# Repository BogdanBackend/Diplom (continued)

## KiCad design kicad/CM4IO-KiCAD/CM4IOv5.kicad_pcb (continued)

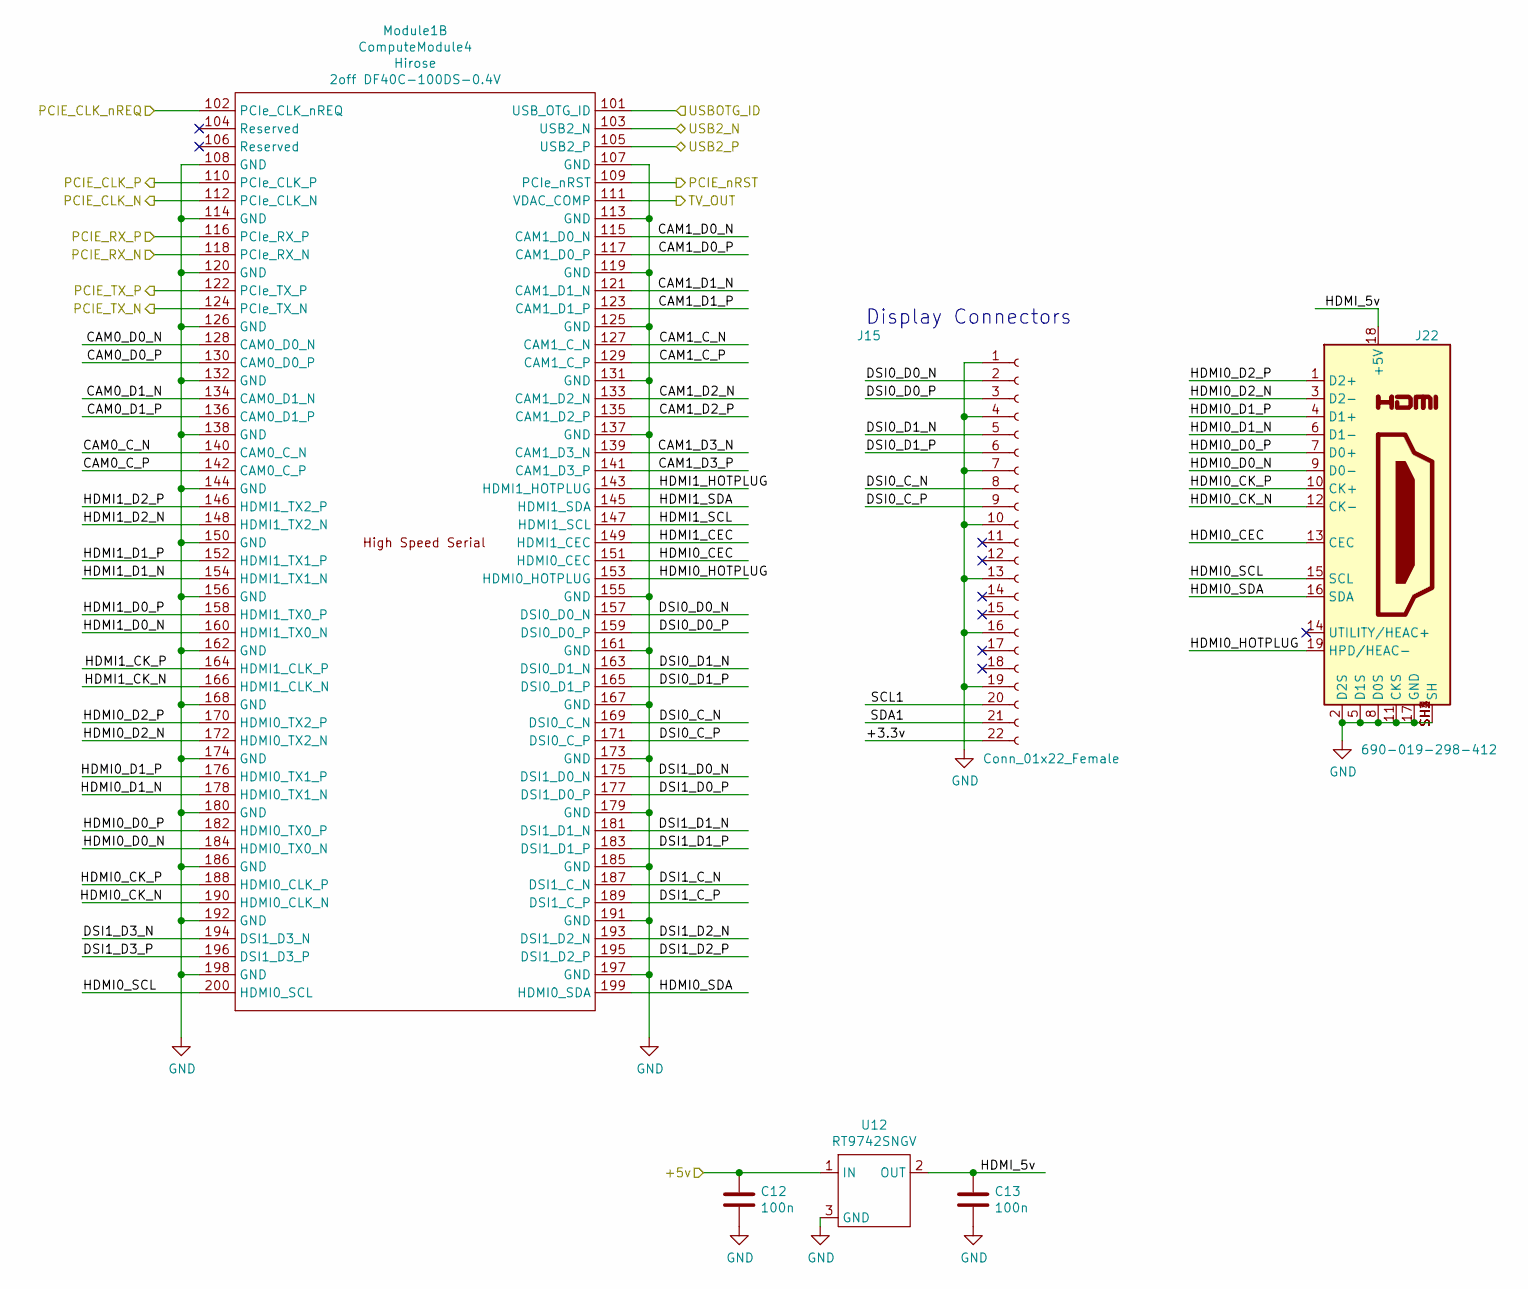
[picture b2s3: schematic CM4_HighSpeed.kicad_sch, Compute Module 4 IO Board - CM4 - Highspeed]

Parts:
C12, C13: 100n; C_0402_1005Metric; Part Description 0.1uF 10% 16V Ceramic Capacitor X7R 040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
J15: Conn_01x22_Female; Hirose_FH12-22S-0.5SH_1x22-1MP_P0.50mm_Horizontal; Part Description 22 Position FFC, FPC Connector Contacts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
J22: 690-019-298-412; EDAC 690-019-298-412; Part Description HDMI Connector, Right Angle, 19 Contact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
Module1: ComputeModule4; Raspberry-Pi-4-Compute-Module; Part Description 100 Position Connector Receptacle, Cent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
U12: RT9742SNGV; SOT-23; Part Description Power Switch/Driver 1:1 N-Channel 500mA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

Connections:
/+5v: C12.1, U12.1 (IN); also elsewhere on the board
/CM4_GPIO ( Ethernet, GPIO, SDCARD)/TV_OUT: Module1.111 (VDAC_COMP); also elsewhere on the board
/CM4_HighSpeed/+3.3v: J15.22
/CM4_HighSpeed/CAM0_C_N: Module1.140 (CAM0_C_N)
/CM4_HighSpeed/CAM0_C_P: Module1.142 (CAM0_C_P)
/CM4_HighSpeed/CAM0_D0_N: Module1.128 (CAM0_D0_N)
/CM4_HighSpeed/CAM0_D0_P: Module1.130 (CAM0_D0_P)
/CM4_HighSpeed/CAM0_D1_N: Module1.134 (CAM0_D1_N)
/CM4_HighSpeed/CAM0_D1_P: Module1.136 (CAM0_D1_P)
/CM4_HighSpeed/CAM1_C_N: Module1.127 (CAM1_C_N)
/CM4_HighSpeed/CAM1_C_P: Module1.129 (CAM1_C_P)
/CM4_HighSpeed/CAM1_D0_N: Module1.115 (CAM1_D0_N)
/CM4_HighSpeed/CAM1_D0_P: Module1.117 (CAM1_D0_P)
/CM4_HighSpeed/CAM1_D1_N: Module1.121 (CAM1_D1_N)
/CM4_HighSpeed/CAM1_D1_P: Module1.123 (CAM1_D1_P)
/CM4_HighSpeed/CAM1_D2_N: Module1.133 (CAM1_D2_N)
/CM4_HighSpeed/CAM1_D2_P: Module1.135 (CAM1_D2_P)
/CM4_HighSpeed/CAM1_D3_N: Module1.139 (CAM1_D3_N)
/CM4_HighSpeed/CAM1_D3_P: Module1.141 (CAM1_D3_P)
/CM4_HighSpeed/DSI0_C_N: J15.8, Module1.169 (DSI0_C_N)
/CM4_HighSpeed/DSI0_C_P: J15.9, Module1.171 (DSI0_C_P)
/CM4_HighSpeed/DSI0_D0_N: J15.2, Module1.157 (DSI0_D0_N)
/CM4_HighSpeed/DSI0_D0_P: J15.3, Module1.159 (DSI0_D0_P)
/CM4_HighSpeed/DSI0_D1_N: J15.5, Module1.163 (DSI0_D1_N)
/CM4_HighSpeed/DSI0_D1_P: J15.6, Module1.165 (DSI0_D1_P)
/CM4_HighSpeed/DSI1_C_N: Module1.187 (DSI1_C_N)
/CM4_HighSpeed/DSI1_C_P: Module1.189 (DSI1_C_P)
/CM4_HighSpeed/DSI1_D0_N: Module1.175 (DSI1_D0_N)
/CM4_HighSpeed/DSI1_D0_P: Module1.177 (DSI1_D0_P)
/CM4_HighSpeed/DSI1_D1_N: Module1.181 (DSI1_D1_N)
/CM4_HighSpeed/DSI1_D1_P: Module1.183 (DSI1_D1_P)
/CM4_HighSpeed/DSI1_D2_N: Module1.193 (DSI1_D2_N)
/CM4_HighSpeed/DSI1_D2_P: Module1.195 (DSI1_D2_P)
/CM4_HighSpeed/DSI1_D3_N: Module1.194 (DSI1_D3_N)
/CM4_HighSpeed/DSI1_D3_P: Module1.196 (DSI1_D3_P)
/CM4_HighSpeed/HDMI0_CEC: J22.13 (CEC), Module1.151 (HDMI0_CEC)
/CM4_HighSpeed/HDMI0_CK_N: J22.12 (CK-), Module1.190 (HDMI0_CLK_N)
/CM4_HighSpeed/HDMI0_CK_P: J22.10 (CK+), Module1.188 (HDMI0_CLK_P)
/CM4_HighSpeed/HDMI0_D0_N: J22.9 (D0-), Module1.184 (HDMI0_TX0_N)
/CM4_HighSpeed/HDMI0_D0_P: J22.7 (D0+), Module1.182 (HDMI0_TX0_P)
/CM4_HighSpeed/HDMI0_D1_N: J22.6 (D1-), Module1.178 (HDMI0_TX1_N)
/CM4_HighSpeed/HDMI0_D1_P: J22.4 (D1+), Module1.176 (HDMI0_TX1_P)
/CM4_HighSpeed/HDMI0_D2_N: J22.3 (D2-), Module1.172 (HDMI0_TX2_N)
/CM4_HighSpeed/HDMI0_D2_P: J22.1 (D2+), Module1.170 (HDMI0_TX2_P)
/CM4_HighSpeed/HDMI0_HOTPLUG: J22.19 (HPD/HEAC-), Module1.153 (HDMI0_HOTPLUG)
/CM4_HighSpeed/HDMI0_SCL: J22.15 (SCL), Module1.200 (HDMI0_SCL)
/CM4_HighSpeed/HDMI0_SDA: J22.16 (SDA), Module1.199 (HDMI0_SDA)
/CM4_HighSpeed/HDMI1_CEC: Module1.149 (HDMI1_CEC)
/CM4_HighSpeed/HDMI1_CK_N: Module1.166 (HDMI1_CLK_N)
/CM4_HighSpeed/HDMI1_CK_P: Module1.164 (HDMI1_CLK_P)
/CM4_HighSpeed/HDMI1_D0_N: Module1.160 (HDMI1_TX0_N)
/CM4_HighSpeed/HDMI1_D0_P: Module1.158 (HDMI1_TX0_P)
/CM4_HighSpeed/HDMI1_D1_N: Module1.154 (HDMI1_TX1_N)
/CM4_HighSpeed/HDMI1_D1_P: Module1.152 (HDMI1_TX1_P)
/CM4_HighSpeed/HDMI1_D2_N: Module1.148 (HDMI1_TX2_N)
/CM4_HighSpeed/HDMI1_D2_P: Module1.146 (HDMI1_TX2_P)
/CM4_HighSpeed/HDMI1_HOTPLUG: Module1.143 (HDMI1_HOTPLUG)
/CM4_HighSpeed/HDMI1_SCL: Module1.147 (HDMI1_SCL)
/CM4_HighSpeed/HDMI1_SDA: Module1.145 (HDMI1_SDA)
/CM4_HighSpeed/HDMI_5v: C13.1, J22.18 (+5V), U12.2 (OUT)
/CM4_HighSpeed/PCIE_CLK_N: Module1.112 (PCIe_CLK_N); also elsewhere on the board
/CM4_HighSpeed/PCIE_CLK_P: Module1.110 (PCIe_CLK_P); also elsewhere on the board
/CM4_HighSpeed/PCIE_CLK_nREQ: Module1.102 (PCIe_CLK_nREQ); also elsewhere on the board
/CM4_HighSpeed/PCIE_RX_N: Module1.118 (PCIe_RX_N); also elsewhere on the board
/CM4_HighSpeed/PCIE_RX_P: Module1.116 (PCIe_RX_P); also elsewhere on the board
/CM4_HighSpeed/PCIE_TX_N: Module1.124 (PCIe_TX_N); also elsewhere on the board
/CM4_HighSpeed/PCIE_TX_P: Module1.122 (PCIe_TX_P); also elsewhere on the board
/CM4_HighSpeed/PCIE_nRST: Module1.109 (PCIe_nRST); also elsewhere on the board
/CM4_HighSpeed/SCL1: J15.20
/CM4_HighSpeed/SDA1: J15.21
/CM4_HighSpeed/USB2_N: Module1.103 (USB2_N); also elsewhere on the board
/CM4_HighSpeed/USB2_P: Module1.105 (USB2_P); also elsewhere on the board
/CM4_HighSpeed/USBOTG_ID: Module1.101 (USB_OTG_ID); also elsewhere on the board
GND: C12.2, C13.2, J15.1, J15.4, J15.7, J15.10, J15.13, J15.16, J15.19, J22.2 (D2S), J22.5 (D1S), J22.8 (D0S), J22.11 (CKS), J22.17 (GND), J22.SH1 (SH), J22.SH2 (SH), J22.SH3 (SH), J22.SH4 (SH), Module1.107 (GND), Module1.108 (GND), Module1.113 (GND), Module1.114 (GND), Module1.119 (GND), Module1.120 (GND), Module1.125 (GND), Module1.126 (GND), Module1.131 (GND), Module1.132 (GND), Module1.137 (GND), Module1.138 (GND), Module1.144 (GND), Module1.150 (GND), Module1.155 (GND), Module1.156 (GND), Module1.161 (GND), Module1.162 (GND), Module1.167 (GND), Module1.168 (GND), Module1.173 (GND), Module1.174 (GND), Module1.179 (GND), Module1.180 (GND), Module1.185 (GND), Module1.186 (GND), Module1.191 (GND), Module1.192 (GND), Module1.197 (GND), Module1.198 (GND), U12.3 (GND); also elsewhere on the board

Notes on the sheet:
Display Connectors

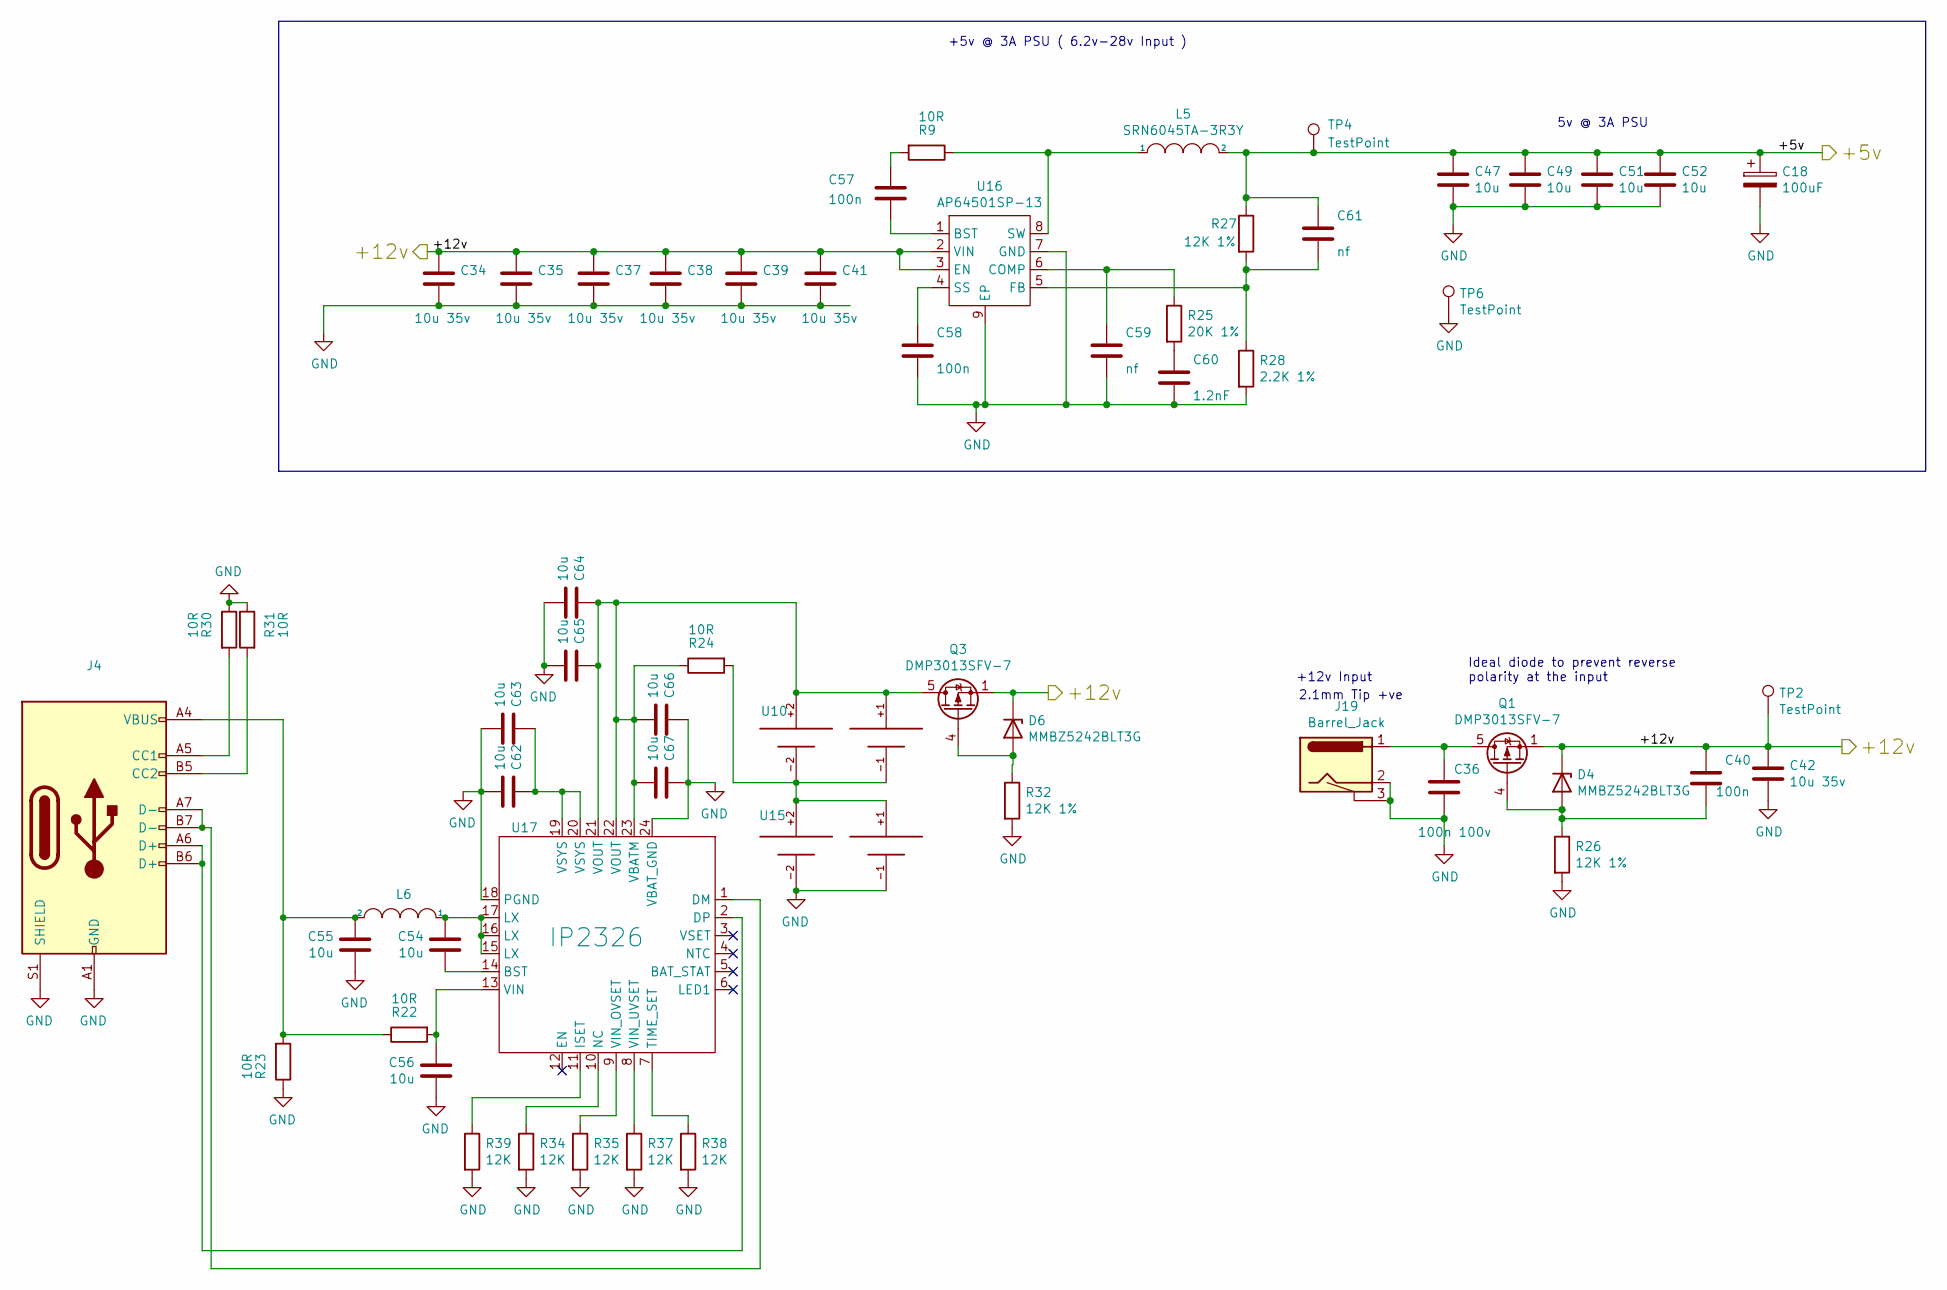
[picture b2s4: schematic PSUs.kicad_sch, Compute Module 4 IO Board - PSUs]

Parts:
C18: 100uF; CP_EIA-7343-31_Kemet-D; Part Description Capacitor, SP-Cap, 100u, 6.3V, 15mR ESR
C34, C35, C37, C38, C39, C41, C42: 10u 35v; C_0805_2012Metric; Part Description 10uF 10% or 20% 35V Ceramic Capacitor X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
C36: 100n 100v; C_0402_1005Metric; Part Description 0.1uF 10% 100V Ceramic Capacitor X5R 04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
C40, C57, C58: 100n; C_0402_1005Metric; Part Description 0.1uF 10% 16V Ceramic Capacitor X7R 040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
C47, C49, C51, C52, C54, C55, C56, C62, C63, C64, C65, C66, C67: 10u; C_0805_2012Metric; Part Description 10uF 10% 10V Ceramic Capacitor X7R 0805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
C59: nf; C_0402_1005Metric
C60: 1.2nF; C_0402_1005Metric; Part Description 1200pF 10% 10V Ceramic Capacitor X5R 04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
C61: nf; C_0402_1005Metric; Part Description 220 pF, 50 V, 0402 [1005 Metric], ± 5%,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
D4, D6: MMBZ5242BLT3G; D_SOT-23_ANK; Part Description Zener Diode 12V 225mW 5% Surface Mount 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
J4: USB_C_Receptacle_USB2.0_14P; USB_C_Receptacle_GCT_USB4135-GF-A_6P_TopMnt_Horizontal
J19: Barrel_Jack; BarrelJack_Horizontal; Part Description DC Power Connectors PCB 2.1MM
L5, L6: SRN6045TA-3R3Y; L_Bourns_SRN6045TA; Part Description 3.3µH Semi-Shielded Wirewound Inductor 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
Q1, Q3: DMP3013SFV-7; Diodes_PowerDI3333-8; Part Description DMP3013SFV-7 - Power MOSFET, P Channel,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
R9, R22, R23, R24, R30, R31: 10R; R_0402_1005Metric; Part Description Resistor 10R M1005 1% 63mW
R25: 20K 1%; R_0402_1005Metric; Part Description Resistor 20K M1005 1% 63mW
R26, R27, R32: 12K 1%; R_0402_1005Metric; Part Description Resistor 12K M1005 1% 63mW
R28: 2.2K 1%; R_0402_1005Metric; Part Description Resistor 2.2K M1005 1% 63mW
R34, R35, R37, R38, R39: 12K; R_0402_1005Metric; Part Description Resistor 12K M1005 1% 63mW
TP2, TP4, TP6: TestPoint; TestPoint_Pad_2.0x2.0mm
U10, U15: BK-18650-PC4; BatteryHolder_MPD_BH-18650-PC2
U16: AP64501SP-13; SOIC-8-1EP_3.9x4.9mm_P1.27mm_EP2.95x4.9mm_Mask2.71x3.4mm_Th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; Part Description Buck Switching Regulator IC Positive Ad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
U17: IP2326; QFN-24-1EP_3x3mm_P0.4mm_EP1.75x1.6mm

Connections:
/+5v: C18.1, C47.1, C49.1, C51.1, C52.1, C61.1, L5.2, R27.1, TP4.1; also elsewhere on the board
/+12v: C34.1, C35.1, C37.1, C38.1, C39.1, C40.1, C41.1, C42.1, D4.1 (K), D6.1 (K), Q1.1 (S), Q1.2 (S), Q1.3 (S), Q3.1 (S), Q3.2 (S), Q3.3 (S), TP2.1, U16.2 (VIN), U16.3 (EN); also elsewhere on the board
GND: C18.2, C34.2, C35.2, C36.2, C37.2, C38.2, C39.2, C41.2, C42.2, C47.2, C49.2, C51.2, C52.2, C55.2, C56.2, C58.2, C59.2, C60.2, C62.2, C63.2, C64.2, C65.2, C66.1, C67.1, J4.A1 (GND), J4.A12 (GND), J4.B1 (GND), J4.B12 (GND), J4.S1 (SHIELD), J19.2, J19.3, R23.1, R26.2, R28.2, R30.1, R31.1, R32.2, R34.2, R35.2, R37.2, R38.2, R39.2, TP6.1, U15.-1, U15.-2, U16.7 (GND), U16.9 (EP), U17.18 (PGND), U17.24 (VBAT_GND); also elsewhere on the board
unnamed: C54.1, L6.1, U17.15 (LX), U17.16 (LX), U17.17 (LX)
unnamed: C55.1, J4.A4 (VBUS), J4.A9 (VBUS), J4.B4 (VBUS), J4.B9 (VBUS), L6.2, R22.1, R23.2
unnamed: C57.1, R9.2
unnamed: C60.1, R25.2
unnamed: C62.1, C63.1, U17.19 (VSYS), U17.20 (VSYS)
unnamed: C40.2, D4.2 (A), Q1.4 (G), R26.1
unnamed: D6.2 (A), Q3.4 (G)
unnamed: J4.A5 (CC1), R30.2
unnamed: J4.B5 (CC2), R31.2
unnamed: C36.1, J19.1, Q1.5 (D)
unnamed: C64.1, C65.1, C66.2, C67.2, Q3.5 (D), R24.1, U10.+1, U10.+2, U17.21 (VOUT), U17.22 (VOUT), U17.23 (VBATM)
unnamed: R24.2, U10.-1, U10.-2, U15.+1, U15.+2
unnamed: C57.2, U16.1 (BST)
unnamed: C59.1, R25.1, U16.6 (COMP)
unnamed: C61.2, R27.2, R28.1, U16.5 (FB)
unnamed: C58.1, U16.4 (SS)
unnamed: L5.1, R9.1, U16.8 (SW)
unnamed: C54.2, U17.14 (BST)
unnamed: J4.A7 (D-), J4.B7 (D-), U17.1 (DM)
unnamed: J4.A6 (D+), J4.B6 (D+), U17.2 (DP)
unnamed: R39.1, U17.11 (ISET)
unnamed: R34.1, U17.10 (NC)
unnamed: R38.1, U17.7 (TIME_SET)
unnamed: C56.1, R22.2, U17.13 (VIN)
unnamed: R35.1, U17.9 (VIN_OVSET)
unnamed: R37.1, U17.8 (VIN_UVSET)

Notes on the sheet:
+12v Input
5v @ 3A PSU
2.1mm Tip +ve
Ideal diode to prevent reverse polarity at the input
+5v @ 3A PSU ( 6.2v-28v Input )

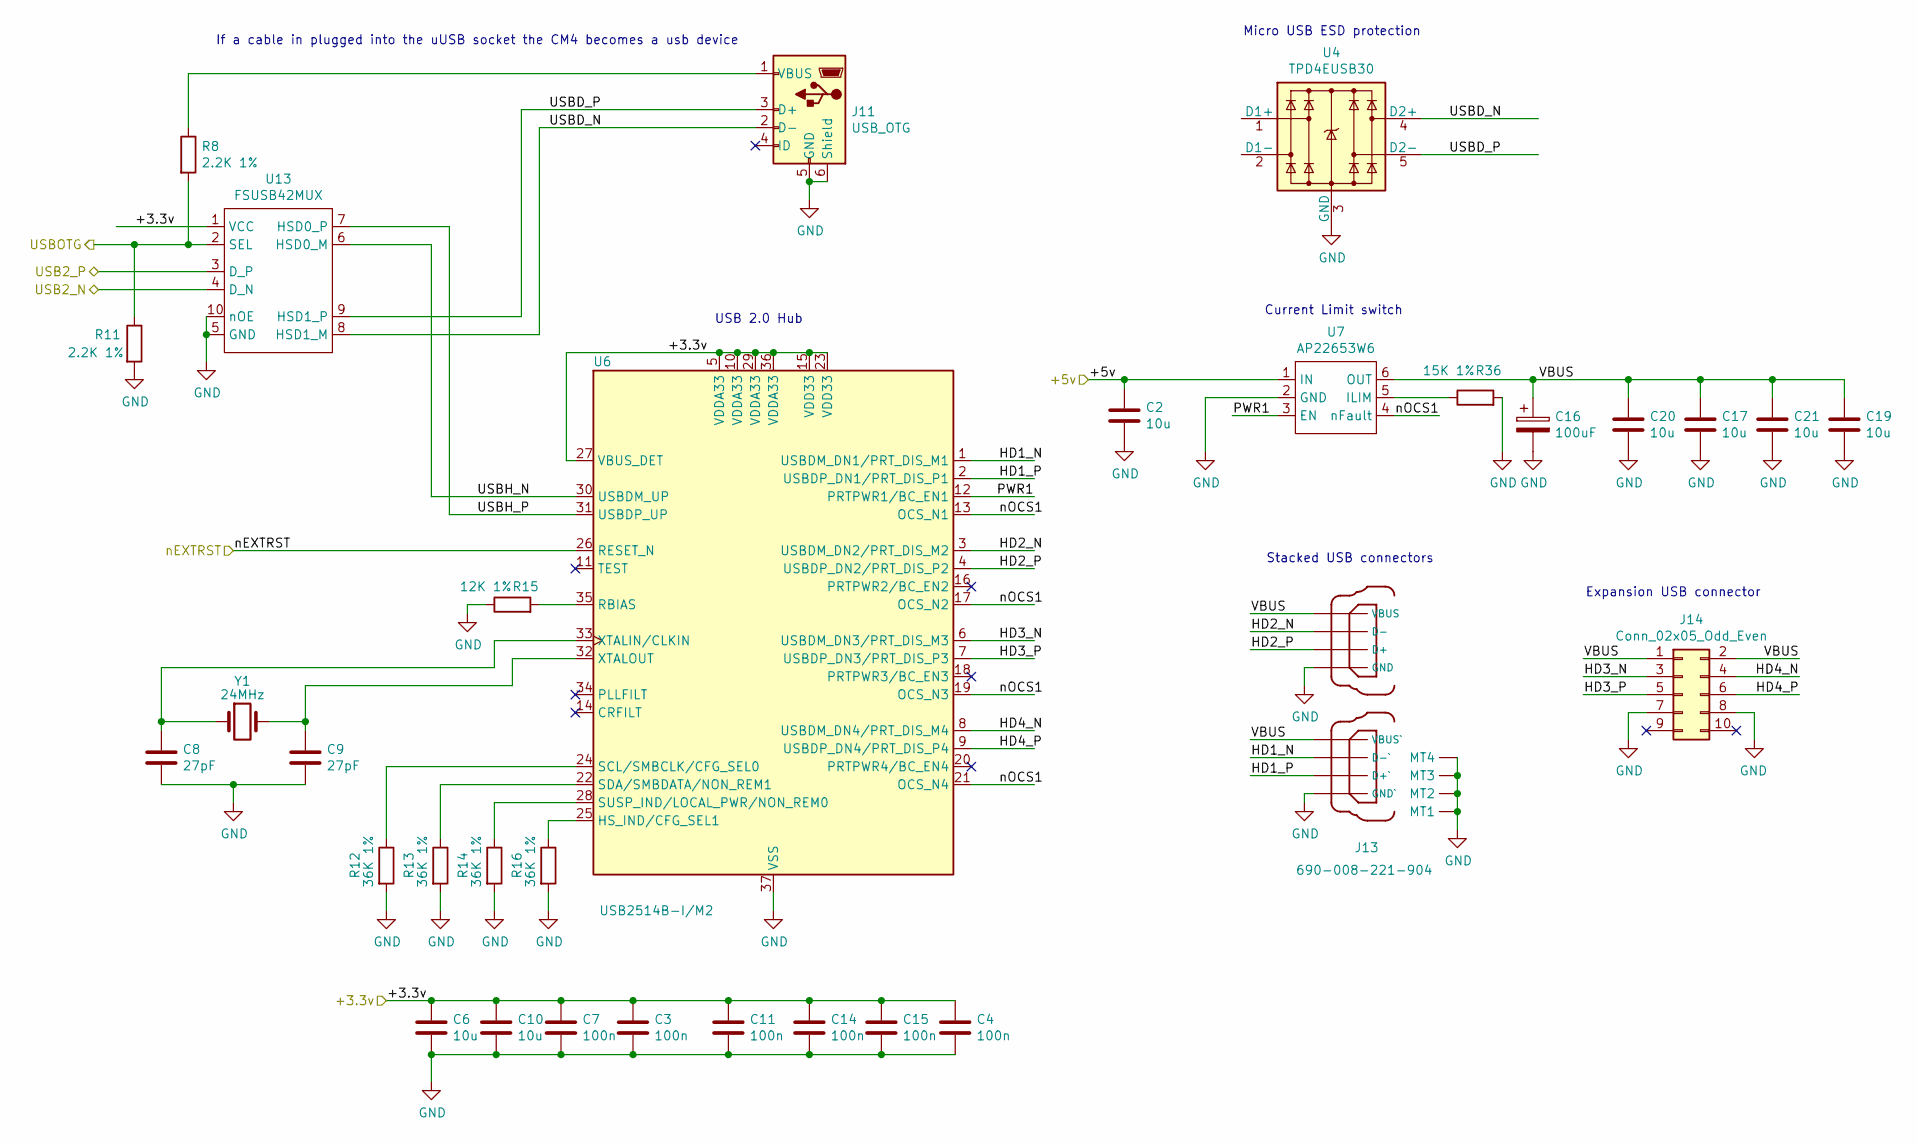
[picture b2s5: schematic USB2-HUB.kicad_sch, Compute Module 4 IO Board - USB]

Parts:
C2, C6, C10, C17, C19, C20, C21: 10u; C_0805_2012Metric; Part Description 10uF 10% 10V Ceramic Capacitor X7R 0805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
C3, C4, C7, C11, C14, C15: 100n; C_0402_1005Metric; Part Description 0.1uF 10% 16V Ceramic Capacitor X7R 040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
C8, C9: 27pF; C_0402_1005Metric; Part Description 27pF 5% 50V Ceramic Capacitor C0G, NP0 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
C16: 100uF; CP_EIA-7343-31_Kemet-D; Part Description Capacitor, SP-Cap, 100u, 6.3V, 15mR ESR
J11: USB_OTG; USB_Micro-B_EDAC_UCON00686; Part Description USB - micro B USB 2.0 Receptacle Connec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
J13: 690-008-221-904; MOLEX_USB_67298-4090; Part Description USB-A (USB TYPE-A), Stacked Receptacle 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
J14: Conn_02x05_Odd_Even; PinHeader_2x05_P2.54mm_Vertical; Part Description PinHeader_2x05_P2.54mm_Vertical
R8, R11: 2.2K 1%; R_0402_1005Metric; Part Description Resistor 2.2K M1005 1% 63mW
R12, R13, R14, R16: 36K 1%; R_0402_1005Metric; Part Description Resistor 36K M1005 1% 63mW
R15: 12K 1%; R_0402_1005Metric; Part Description Resistor 12K M1005 1% 63mW
R36: 15K 1%; R_0402_1005Metric; Part Description Resistor 15K M1005 1% 63mW
U4: TPD4EUSB30; USON-10_2.5x1.0mm_P0.5mm; Part Description Quad TVS diode for high speed signals (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
U6: USB2514B-I/M2; QFN-36-1EP_6x6mm_P0.5mm_EP3.7x3.7mm; Part Description USB Hub Controller USB Interface 36-SQF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
U7: AP22653W6; SOT-23-6; Part Description Power Switch/Driver 1:1 P-Channel 2.1A 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
U13: FSUSB42MUX; MSOP-10_3x3mm_P0.5mm; Part Description USB Switch IC 1 Channel 10-MSOP
Y1: 24MHz; Crystal_SMD_HC49-SD; Part Description 24MHz Crystal 18pf 30ppm 30ppm

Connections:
/+3.3v: C3.1, C4.1, C6.1, C7.1, C10.1, C11.1, C14.1, C15.1, U6.5 (VDDA33), U6.10 (VDDA33), U6.15 (VDD33), U6.23 (VDD33), U6.27 (VBUS_DET), U6.29 (VDDA33), U6.36 (VDDA33), U13.1 (VCC); also elsewhere on the board
/+5v: C2.1, U7.1 (IN); also elsewhere on the board
/CM4_HighSpeed/USB2_N: U13.4 (D_N); also elsewhere on the board
/CM4_HighSpeed/USB2_P: U13.3 (D_P); also elsewhere on the board
/CM4_HighSpeed/USBOTG_ID: R8.2, R11.1, U13.2 (SEL); also elsewhere on the board
/USB2-HUB/HD1_N: J13.2 (D-`), U6.1 (USBDM_DN1/PRT_DIS_M1)
/USB2-HUB/HD1_P: J13.3 (D+`), U6.2 (USBDP_DN1/PRT_DIS_P1)
/USB2-HUB/HD2_N: J13.6 (D-), U6.3 (USBDM_DN2/PRT_DIS_M2)
/USB2-HUB/HD2_P: J13.7 (D+), U6.4 (USBDP_DN2/PRT_DIS_P2)
/USB2-HUB/HD3_N: J14.3, U6.6 (USBDM_DN3/PRT_DIS_M3)
/USB2-HUB/HD3_P: J14.5, U6.7 (USBDP_DN3/PRT_DIS_P3)
/USB2-HUB/HD4_N: J14.4, U6.8 (USBDM_DN4/PRT_DIS_M4)
/USB2-HUB/HD4_P: J14.6, U6.9 (USBDP_DN4/PRT_DIS_P4)
/USB2-HUB/PWR1: U6.12 (PRTPWR1/BC_EN1), U7.3 (EN)
/USB2-HUB/USBD_N: J11.2 (D-), U4.4 (D2+), U4.7, U13.8 (HSD1_M)
/USB2-HUB/USBD_P: J11.3 (D+), U4.5 (D2-), U4.6, U13.9 (HSD1_P)
/USB2-HUB/USBH_N: U6.30 (USBDM_UP), U13.6 (HSD0_M)
/USB2-HUB/USBH_P: U6.31 (USBDP_UP), U13.7 (HSD0_P)
/USB2-HUB/VBUS: C16.1, C17.1, C19.1, C20.1, C21.1, J13.1 (VBUS`), J13.5 (VBUS), J14.1, J14.2, U7.6 (OUT)
/USB2-HUB/nOCS1: U6.13 (OCS_N1), U6.17 (OCS_N2), U6.19 (OCS_N3), U6.21 (OCS_N4), U7.4 (nFault)
/nEXTRST: U6.26 (RESET_N); also elsewhere on the board
GND: C2.2, C3.2, C4.2, C6.2, C7.2, C8.2, C9.2, C10.2, C11.2, C14.2, C15.2, C16.2, C17.2, C19.2, C20.2, C21.2, J11.5 (GND), J11.6 (Shield), J13.4 (GND`), J13.8 (GND), J13.MT1, J13.MT2, J13.MT3, J13.MT4, J14.7, J14.8, R11.2, R12.2, R13.2, R14.2, R15.1, R16.2, R36.2, U4.3 (GND), U4.8 (GND), U6.37 (VSS), U7.2 (GND), U13.5 (GND), U13.10 (nOE); also elsewhere on the board
unnamed: J11.1 (VBUS), R8.1
unnamed: U4.1 (D1+), U4.10
unnamed: U4.2 (D1-), U4.9
unnamed: R16.1, U6.25 (HS_IND/CFG_SEL1)
unnamed: R15.2, U6.35 (RBIAS)
unnamed: R12.1, U6.24 (SCL/SMBCLK/CFG_SEL0)
unnamed: R13.1, U6.22 (SDA/SMBDATA/NON_REM1)
unnamed: R14.1, U6.28 (SUSP_IND/LOCAL_PWR/NON_REM0)
unnamed: C8.1, U6.33 (XTALIN/CLKIN), Y1.1
unnamed: C9.1, U6.32 (XTALOUT), Y1.2
unnamed: R36.1, U7.5 (ILIM)

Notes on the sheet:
Expansion USB connector
Current Limit switch
USB 2.0 Hub
If a cable in plugged into the uUSB socket the CM4 becomes a usb device
Micro USB ESD protection
Stacked USB connectors

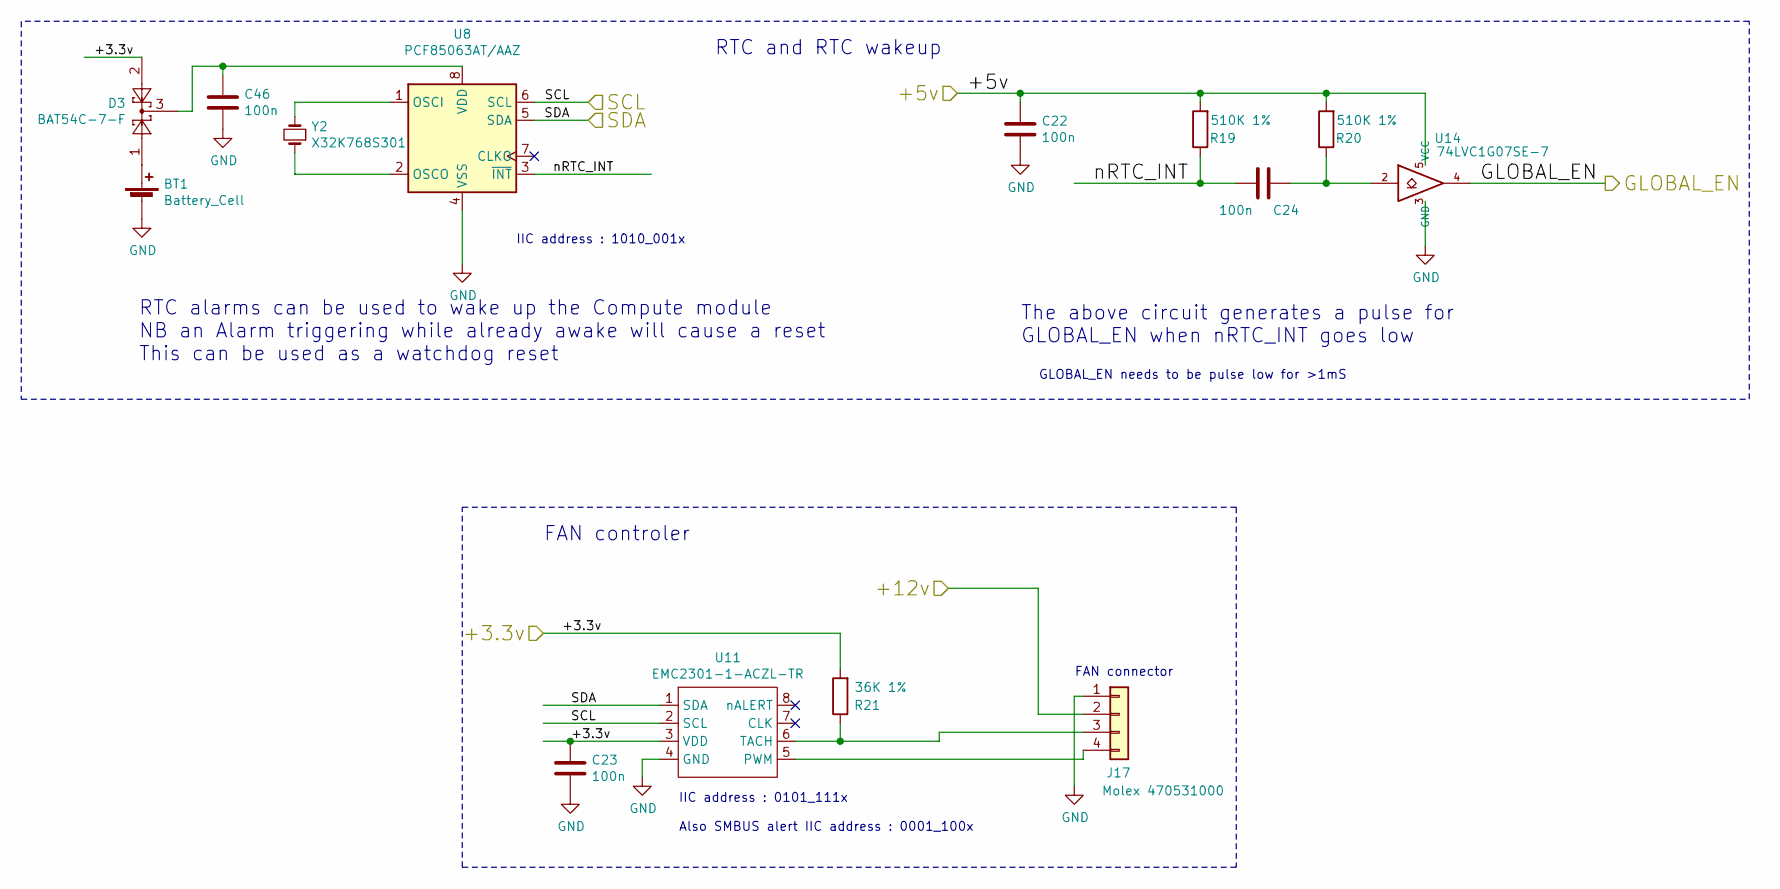
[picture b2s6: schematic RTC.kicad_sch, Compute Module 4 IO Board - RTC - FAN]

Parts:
BT1: Battery_Cell; BatteryHolder_Keystone_3034_1x20mm; Part Description Battery Retainer Coin, 20.0mm 1 Cell SM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
C22, C23, C24, C46: 100n; C_0402_1005Metric; Part Description 0.1uF 10% 16V Ceramic Capacitor X7R 040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
D3: BAT54C-7-F; SOT-23; Part Description Diode Array 1 Pair Common Cathode Schot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
J17: Molex 470531000; FanPinHeader_1x04_P2.54mm_Vertical; Part Description Connector Header Through Hole 4 positio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
R19, R20: 510K 1%; R_0402_1005Metric; Part Description Resistor 510K M1005 1% 63mW
R21: 36K 1%; R_0402_1005Metric; Part Description Resistor 36K M1005 1% 63mW
U8: PCF85063AT/AAZ; SOIC-8_3.9x4.9mm_P1.27mm; Part Description Real Time Clock (RTC) IC Clock/Calendar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
U11: EMC2301-1-ACZL-TR; MSOP-8_3x3mm_P0.65mm; Part Description Motor Driver PWM 8-MSOP
U14: 74LVC1G07SE-7; SOT-353_SC-70-5; Part Description Buffer, Non-Inverting 1 Element 1 Bit p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
Y2: X32K768S301; Crystal_SMD_3215-2Pin_3.2x1.5mm; Part Description Crystal 32.768KHz 7pF 20pmm

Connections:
/+3.3v: C23.1, D3.2, R21.2, U11.3 (VDD); also elsewhere on the board
/+5v: C22.1, R19.2, R20.2, U14.5 (VCC); also elsewhere on the board
/+12v: J17.2; also elsewhere on the board
/CM4_GPIO ( Ethernet, GPIO, SDCARD)/GLOBAL_EN: U14.4; also elsewhere on the board
/RTC , Wakeup, FAN/SCL: U8.6 (SCL), U11.2 (SCL); also elsewhere on the board
/RTC , Wakeup, FAN/SDA: U8.5 (SDA), U11.1 (SDA); also elsewhere on the board
/RTC , Wakeup, FAN/nRTC_INT: C24.2, R19.1, U8.3 (~INT)
GND: BT1.2 (-), C22.2, C23.2, C46.2, J17.1, U8.4 (VSS), U11.4 (GND), U14.3 (GND); also elsewhere on the board
unnamed: BT1.1 (+), D3.1
unnamed: C24.1, R20.1, U14.2
unnamed: J17.3, R21.1, U11.6 (TACH)
unnamed: J17.4, U11.5 (PWM)
unnamed: U8.1 (OSCI), Y2.2
unnamed: U8.2 (OSCO), Y2.1
unnamed: C46.1, D3.3, U8.8 (VDD)

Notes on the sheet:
RTC alarms can be used to wake up the Compute module NB an Alarm triggering while already awake will cause a reset This can be used as a watchdog reset
RTC and RTC wakeup
Also SMBUS alert IIC address : 0001_100x
IIC address : 0101_111x
IIC address : 1010_001x
GLOBAL_EN needs to be pulse low for >1mS
FAN controler
FAN connector
The above circuit generates a pulse for GLOBAL_EN when nRTC_INT goes low

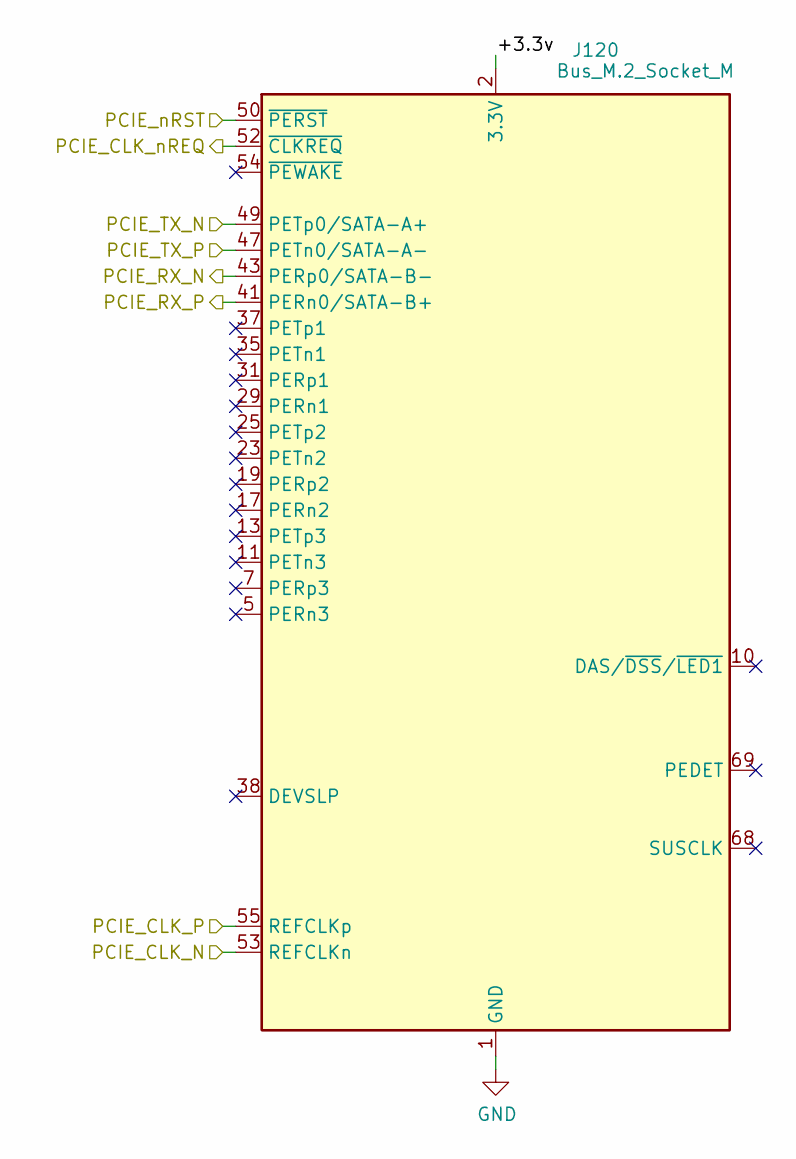
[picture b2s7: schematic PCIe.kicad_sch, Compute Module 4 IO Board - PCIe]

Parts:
J120: Bus_M.2_Socket_M; M2

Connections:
/CM4_HighSpeed/PCIE_CLK_N: J120.53 (REFCLKn); also elsewhere on the board
/CM4_HighSpeed/PCIE_CLK_P: J120.55 (REFCLKp); also elsewhere on the board
/CM4_HighSpeed/PCIE_CLK_nREQ: J120.52 (~CLKREQ); also elsewhere on the board
/CM4_HighSpeed/PCIE_RX_N: J120.43 (PERp0/SATA-B-); also elsewhere on the board
/CM4_HighSpeed/PCIE_RX_P: J120.41 (PERn0/SATA-B+); also elsewhere on the board
/CM4_HighSpeed/PCIE_TX_N: J120.49 (PETp0/SATA-A+); also elsewhere on the board
/CM4_HighSpeed/PCIE_TX_P: J120.47 (PETn0/SATA-A-); also elsewhere on the board
/CM4_HighSpeed/PCIE_nRST: J120.50 (~PERST); also elsewhere on the board
/PCIe-connector/+3.3v: J120.2 (3.3V), J120.4 (3.3V), J120.12 (3.3V), J120.14 (3.3V), J120.16 (3.3V), J120.18 (3.3V), J120.70 (3.3V), J120.72 (3.3V), J120.74 (3.3V)
GND: J120.1 (GND), J120.3 (GND), J120.9 (GND), J120.15 (GND), J120.21 (GND), J120.27 (GND), J120.33 (GND), J120.39 (GND), J120.45 (GND), J120.51 (GND), J120.57 (GND), J120.71 (GND), J120.73 (GND), J120.75 (GND); also elsewhere on the board

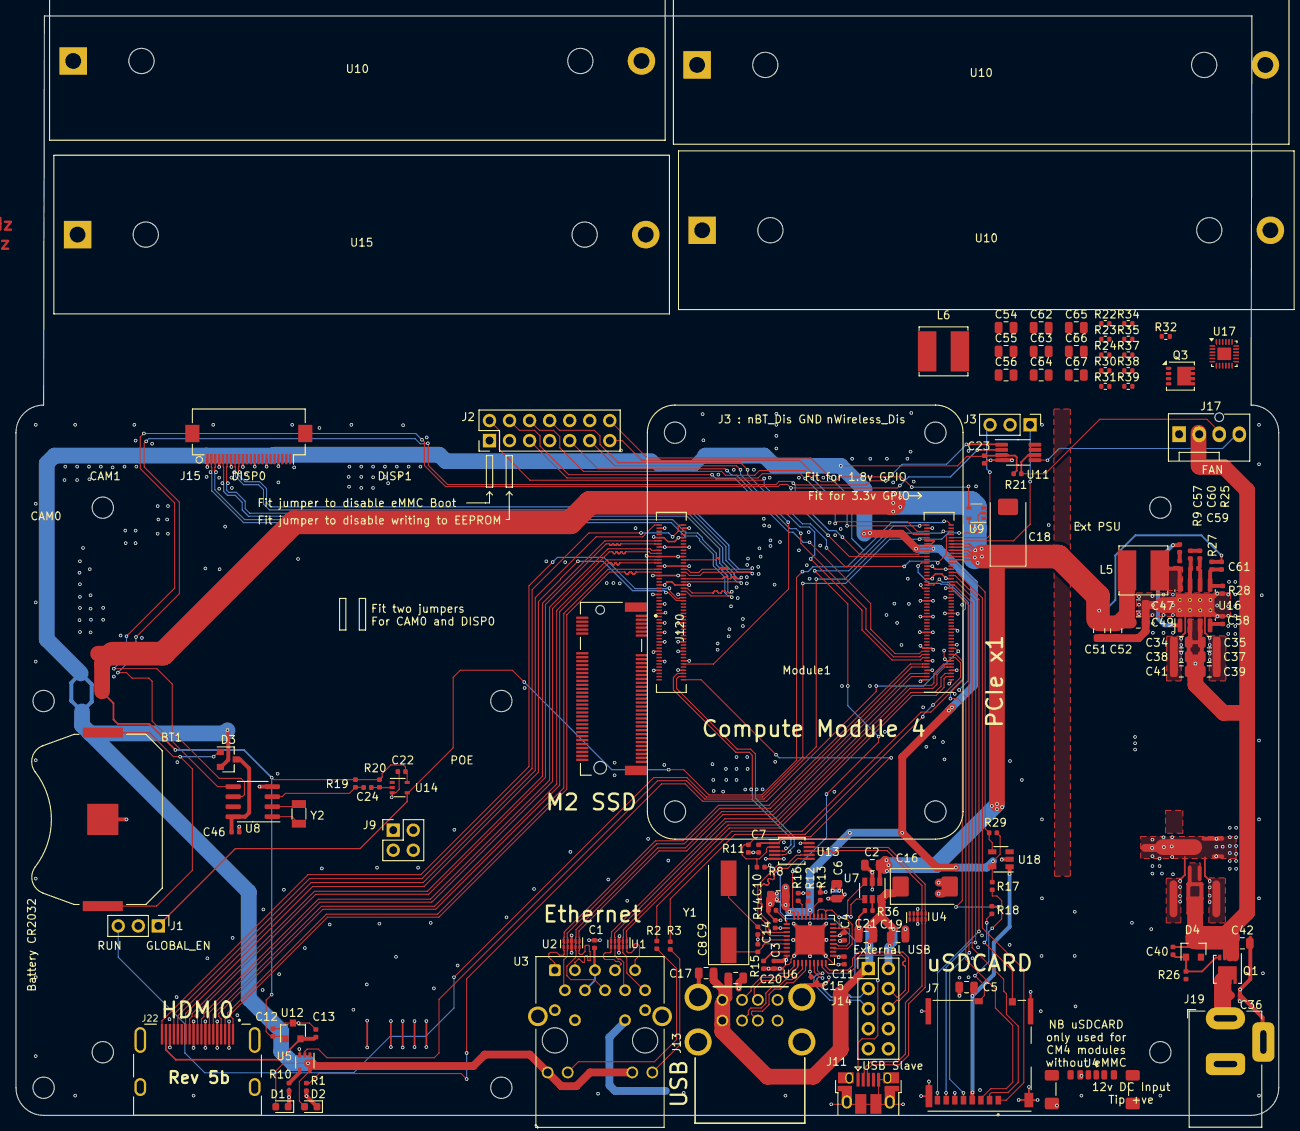
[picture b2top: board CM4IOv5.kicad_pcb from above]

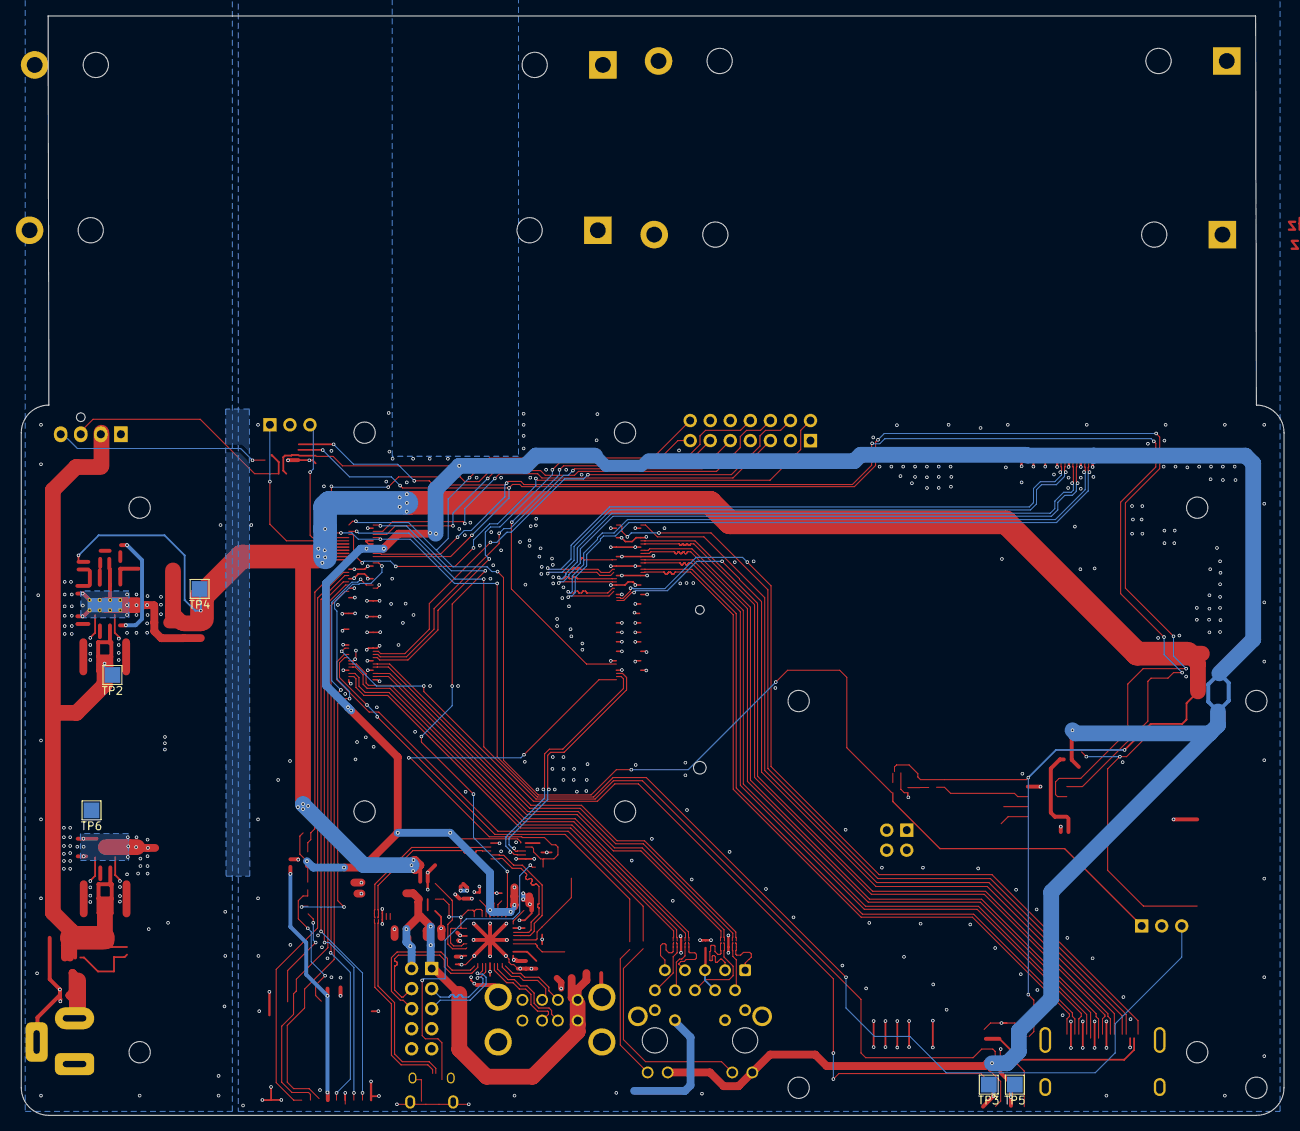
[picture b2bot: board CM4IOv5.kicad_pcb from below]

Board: 4 copper layers, 160.0 x 139.3 mm, 145 parts (5 on the bottom side), 140 nets.

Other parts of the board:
U10#2, U10#3: BK-18650-PC4; BatteryHolder_MPD_BH-18650-PC2

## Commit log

2025-01-31 edit chapters
2025-03-21 thesis
2025-05-06 1-4 some changes
2025-05-07 4 need more imgs
2025-05-09 принципова
2025-05-09 ReadMee kicad
2025-05-09 принципова imgs
2025-05-11 md2docx v2
2025-05-14 model
2025-05-14 add draw
2025-05-14 практика
2025-05-14 приколи з py
2025-05-14 no pdf
2025-05-14 md_links
2025-05-14 md_link
2025-05-14 add self url md_link
2025-05-14 move old
2025-05-14 test pdf
2025-05-14 edit links
2025-05-14 try docx.py
2025-05-14 maybe docx.md
2025-05-14 final md2.py?
2025-05-15 md2 ламає docx для libre office ((
2025-05-15 edit style
2025-05-15 style
2025-05-15 best 2docx
2025-05-15 best2
2025-05-15 edit template
2025-05-15 some fix
2025-05-15 fix2
2025-05-15 final v0.3
2025-05-15 readme edit
2025-05-15 minor
2025-05-16 add recomend py
2025-05-16 prac 1
2025-05-16 plan 0
2025-05-16 prac 0,1 full
2025-05-16 prac v dev
2025-05-16 final? prac
2025-05-16 some summarize
2025-05-18 hack
2025-05-19 some splell checking
2025-05-19 super fix BladeRF
2025-05-19 - style
2025-05-19 chapter change
2025-05-19 fix thesis
2025-05-19 CHANGE TREE DIRECTORY
2025-05-19 fo github Pages
2025-05-19 github pages
2025-05-19 edits chapters
2025-05-19 global restructure
2025-05-20 1-3 ch add some summarize
2025-05-21 link edit
2025-05-22 change kicad
2025-05-22 fix style, add screenshots KiCAD
2025-05-22 add experimental
2025-05-22 diplom_template replace
2025-05-22 структурна
2025-05-22 pre final
2025-05-23 plag check
2025-05-26 y changes
2025-05-26 fix 2docx
2025-05-27 Pending changes exported from your codespace
2025-05-30 electrick part
2025-05-30 electric part xlsx
2025-05-30 p edit
2025-05-30 pre_pre final
2025-06-01 >100 pages ):
2025-06-01 74 page
2025-06-01 73page+plagCheck
2025-06-03 final
2025-06-04 final?
2025-06-04 final??
2025-06-06 windows reorganisation
2025-06-06 win Broken simlink
